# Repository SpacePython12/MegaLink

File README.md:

# MegaLink
A Megadrive/Genesis cartridge that connects to your computer!

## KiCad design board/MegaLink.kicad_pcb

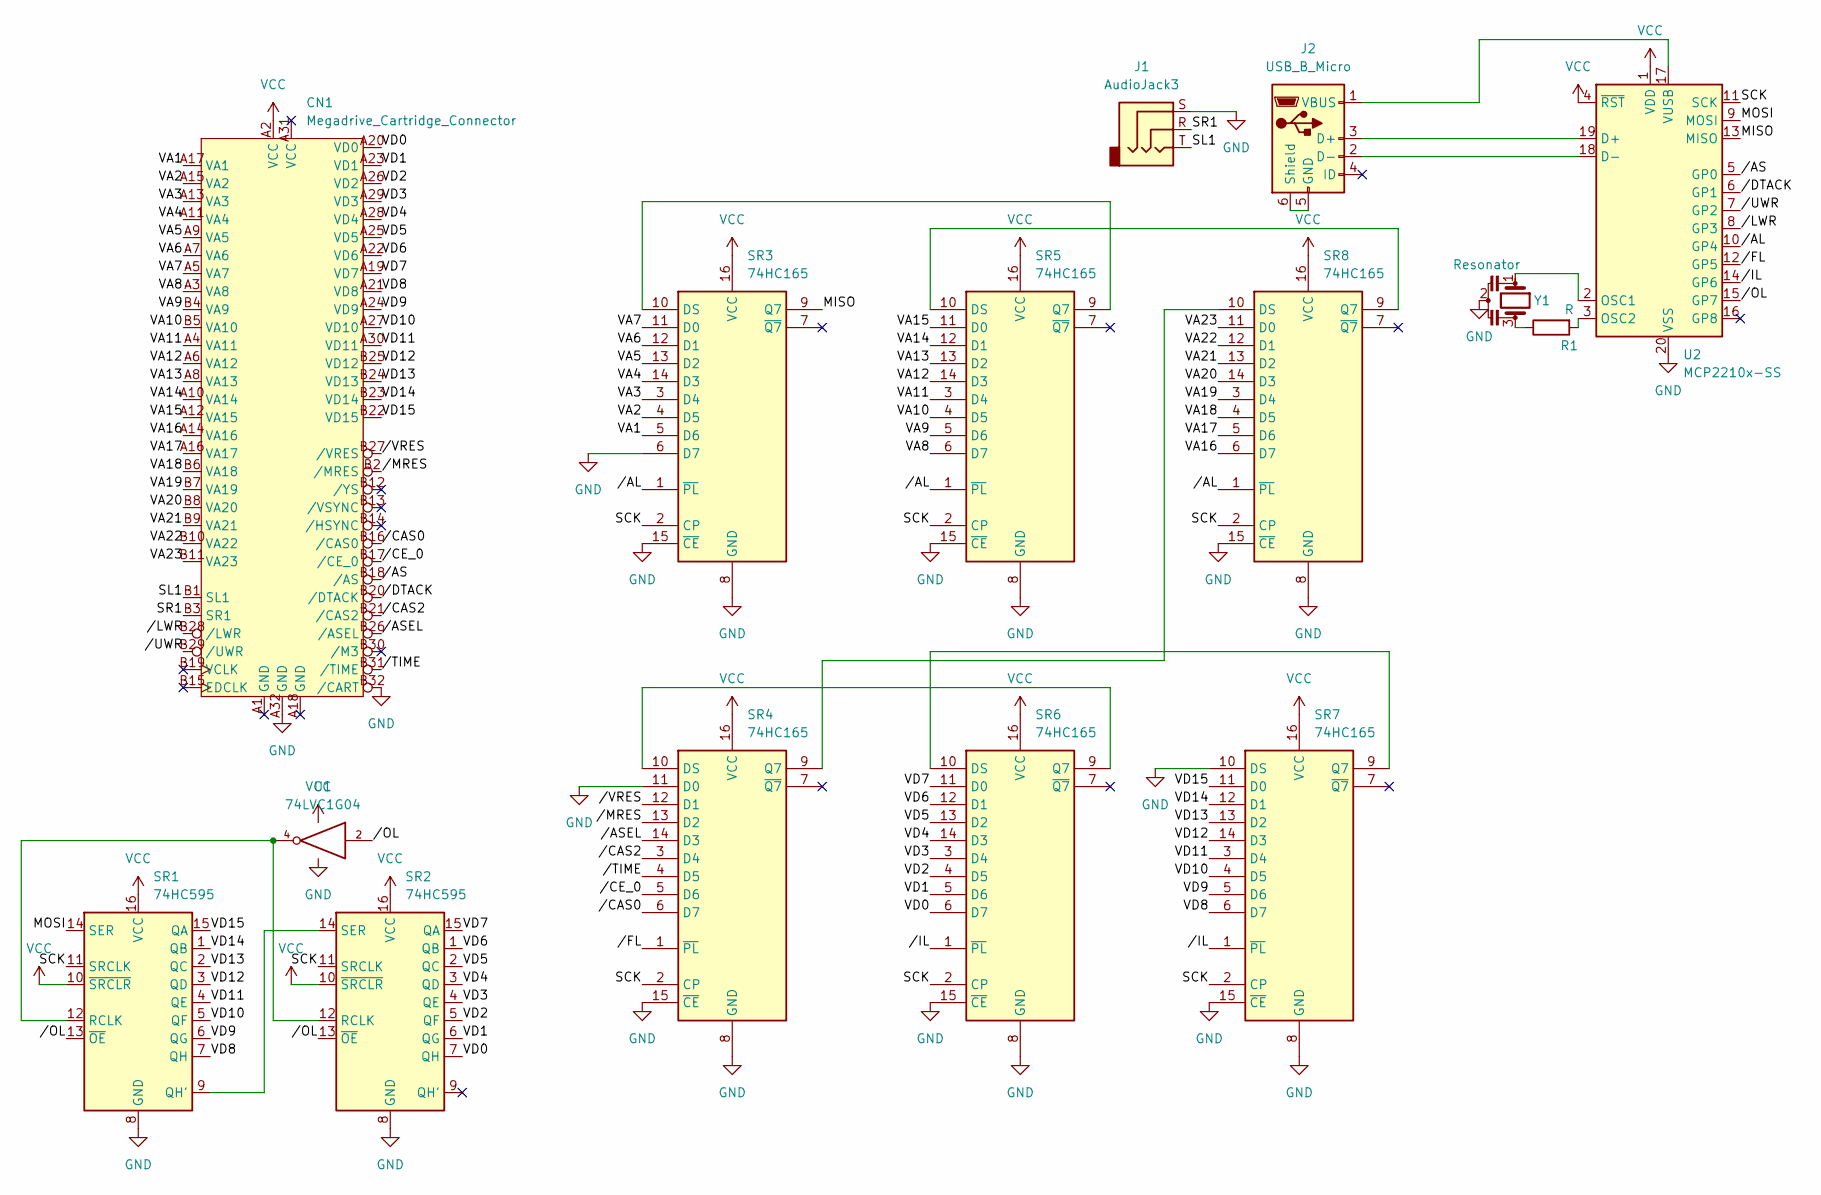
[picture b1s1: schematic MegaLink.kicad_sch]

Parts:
CN1: Megadrive_Cartridge_Connector; Megadrive Cartridge Connector
J1: AudioJack3; Jack_3.5mm_CUI_SJ-3523-SMT_Horizontal
J2: USB_B_Micro; USB_Micro-B_Molex-105017-0001
R1: R; R_Axial_DIN0204_L3.6mm_D1.6mm_P5.08mm_Horizontal
SR1, SR2: 74HC595; 74HC165_SO16
SR3, SR4, SR5, SR6, SR7, SR8: 74HC165; 74HC165_SO16
U1: 74LVC1G04; Logic_DRL
U2: MCP2210x-SS; SSOP-20_5.3x7.2mm_P0.65mm
Y1: Resonator

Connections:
/MISO: SR3.9 (Q7), U2.13 (MISO)
/MOSI: SR1.14 (SER), U2.9 (MOSI)
/SCK: SR1.11 (SRCLK), SR2.11 (SRCLK), SR3.2 (CP), SR4.2 (CP), SR5.2 (CP), SR6.2 (CP), SR7.2 (CP), SR8.2 (CP), U2.11 (SCK)
/SL1: CN1.B1 (SL1), J1.T
/SR1: CN1.B3 (SR1), J1.R
/VA1: CN1.A17 (VA1), SR3.5 (D6)
/VA2: CN1.A15 (VA2), SR3.4 (D5)
/VA3: CN1.A13 (VA3), SR3.3 (D4)
/VA4: CN1.A11 (VA4), SR3.14 (D3)
/VA5: CN1.A9 (VA5), SR3.13 (D2)
/VA6: CN1.A7 (VA6), SR3.12 (D1)
/VA7: CN1.A5 (VA7), SR3.11 (D0)
/VA8: CN1.A3 (VA8), SR5.6 (D7)
/VA9: CN1.B4 (VA9), SR5.5 (D6)
/VA10: CN1.B5 (VA10), SR5.4 (D5)
/VA11: CN1.A4 (VA11), SR5.3 (D4)
/VA12: CN1.A6 (VA12), SR5.14 (D3)
/VA13: CN1.A8 (VA13), SR5.13 (D2)
/VA14: CN1.A10 (VA14), SR5.12 (D1)
/VA15: CN1.A12 (VA15), SR5.11 (D0)
/VA16: CN1.A14 (VA16), SR8.6 (D7)
/VA17: CN1.A16 (VA17), SR8.5 (D6)
/VA18: CN1.B6 (VA18), SR8.4 (D5)
/VA19: CN1.B7 (VA19), SR8.3 (D4)
/VA20: CN1.B8 (VA20), SR8.14 (D3)
/VA21: CN1.B9 (VA21), SR8.13 (D2)
/VA22: CN1.B10 (VA22), SR8.12 (D1)
/VA23: CN1.B11 (VA23), SR8.11 (D0)
/VD0: CN1.A20 (VD0), SR2.7 (QH), SR6.6 (D7)
/VD1: CN1.A23 (VD1), SR2.6 (QG), SR6.5 (D6)
/VD2: CN1.A26 (VD2), SR2.5 (QF), SR6.4 (D5)
/VD3: CN1.A29 (VD3), SR2.4 (QE), SR6.3 (D4)
/VD4: CN1.A28 (VD4), SR2.3 (QD), SR6.14 (D3)
/VD5: CN1.A25 (VD5), SR2.2 (QC), SR6.13 (D2)
/VD6: CN1.A22 (VD6), SR2.1 (QB), SR6.12 (D1)
/VD7: CN1.A19 (VD7), SR2.15 (QA), SR6.11 (D0)
/VD8: CN1.A21 (VD8), SR1.7 (QH), SR7.6 (D7)
/VD9: CN1.A24 (VD9), SR1.6 (QG), SR7.5 (D6)
/VD10: CN1.A27 (VD10), SR1.5 (QF), SR7.4 (D5)
/VD11: CN1.A30 (VD11), SR1.4 (QE), SR7.3 (D4)
/VD12: CN1.B25 (VD12), SR1.3 (QD), SR7.14 (D3)
/VD13: CN1.B24 (VD13), SR1.2 (QC), SR7.13 (D2)
/VD14: CN1.B23 (VD14), SR1.1 (QB), SR7.12 (D1)
/VD15: CN1.B22 (VD15), SR1.15 (QA), SR7.11 (D0)
//AL: SR3.1 (~PL), SR5.1 (~PL), SR8.1 (~PL), U2.10 (GP4)
//AS: CN1.B18 (/AS), U2.5 (GP0)
//ASEL: CN1.B26 (/ASEL), SR4.14 (D3)
//CAS0: CN1.B16 (/CAS0), SR4.6 (D7)
//CAS2: CN1.B21 (/CAS2), SR4.3 (D4)
//CE_0: CN1.B17 (/CE_0), SR4.5 (D6)
//DTACK: CN1.B20 (/DTACK), U2.6 (GP1)
//FL: SR4.1 (~PL), U2.12 (GP5)
//IL: SR6.1 (~PL), SR7.1 (~PL), U2.14 (GP6)
//LWR: CN1.B28 (/LWR), U2.8 (GP3)
//MRES: CN1.B2 (/MRES), SR4.13 (D2)
//OL: SR1.13 (~OE), SR2.13 (~OE), U1.2, U2.15 (GP7)
//TIME: CN1.B31 (/TIME), SR4.4 (D5)
//UWR: CN1.B29 (/UWR), U2.7 (GP2)
//VRES: CN1.B27 (/VRES), SR4.12 (D1)
GND: CN1.A32 (GND), CN1.B32 (/CART), J1.S, SR1.8 (GND), SR2.8 (GND), SR3.6 (D7), SR3.8 (GND), SR3.15 (~CE), SR4.8 (GND), SR4.11 (D0), SR4.15 (~CE), SR5.8 (GND), SR5.15 (~CE), SR6.8 (GND), SR6.15 (~CE), SR7.8 (GND), SR7.10 (DS), SR7.15 (~CE), SR8.8 (GND), SR8.15 (~CE), U1.3 (GND), U2.20 (VSS), Y1.2
unnamed: J2.1 (VBUS), U2.17 (VUSB)
unnamed: J2.2 (D-), U2.18 (D-)
unnamed: J2.3 (D+), U2.19 (D+)
unnamed: J2.5 (GND), J2.6 (Shield)
unnamed: R1.1, Y1.3
unnamed: R1.2, U2.3 (OSC2)
unnamed: SR1.12 (RCLK), SR2.12 (RCLK), U1.4
unnamed: SR1.9 (QH'), SR2.14 (SER)
unnamed: SR3.10 (DS), SR5.9 (Q7)
unnamed: SR4.9 (Q7), SR8.10 (DS)
unnamed: SR4.10 (DS), SR6.9 (Q7)
unnamed: SR5.10 (DS), SR8.9 (Q7)
unnamed: SR6.10 (DS), SR7.9 (Q7)
unnamed: U2.2 (OSC1), Y1.1
VCC: CN1.A2 (VCC), SR1.10 (~SRCLR), SR1.16 (VCC), SR2.10 (~SRCLR), SR2.16 (VCC), SR3.16 (VCC), SR4.16 (VCC), SR5.16 (VCC), SR6.16 (VCC), SR7.16 (VCC), SR8.16 (VCC), U1.5 (VCC), U2.1 (VDD), U2.4 (~RST)

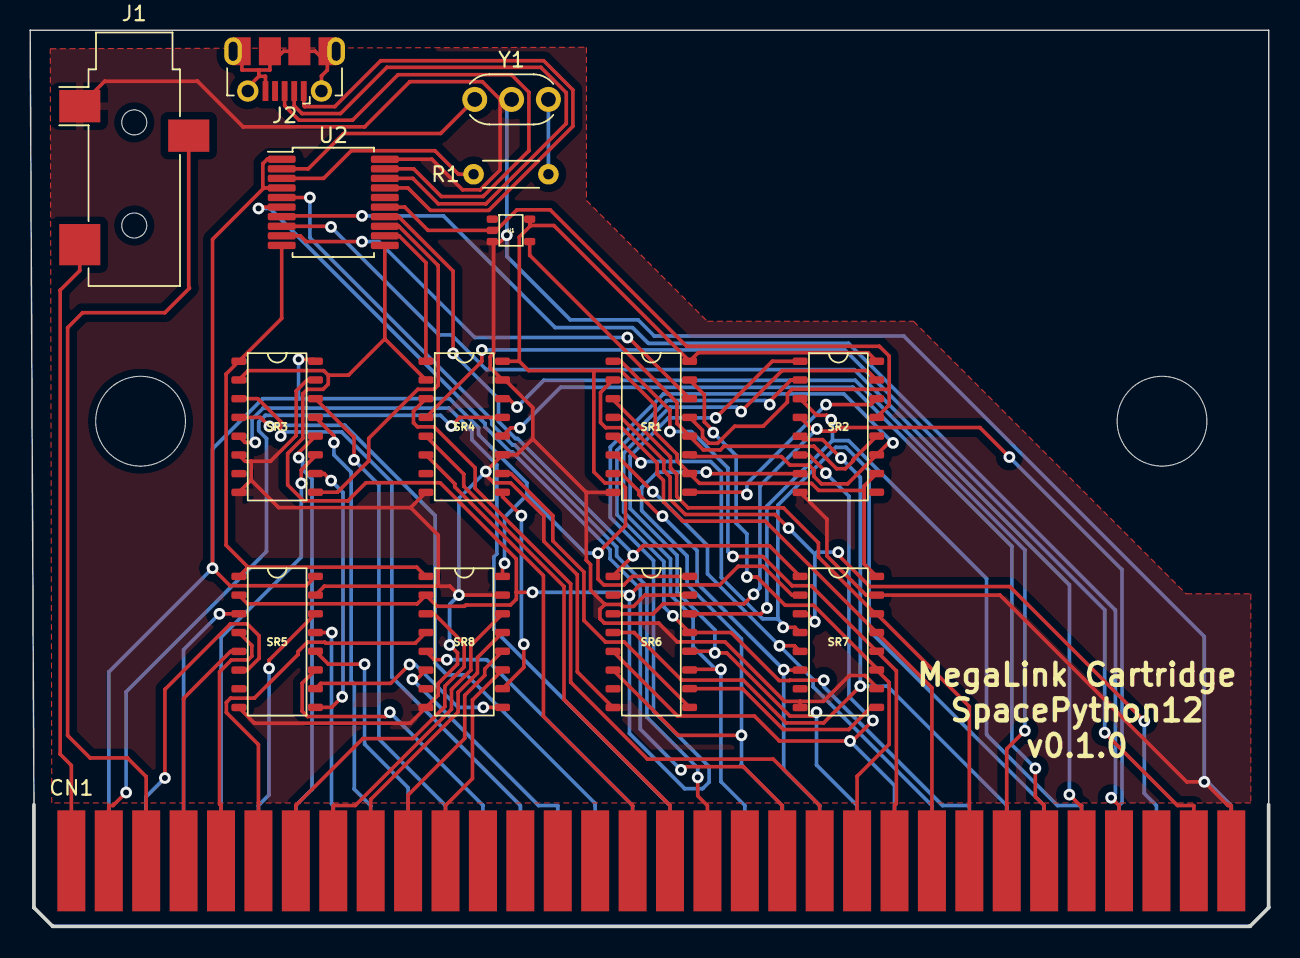
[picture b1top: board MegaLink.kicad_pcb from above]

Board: 2 copper layers, 84.0 x 60.8 mm, 15 parts (0 on the bottom side), 75 nets.

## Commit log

2022-11-29 More files
2022-11-29 Even more files and dir management
